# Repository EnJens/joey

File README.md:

# Joey 

Joey is an ECP5 with a 50-pin FPC connector intended to be used as a 
breakout development board for high-pin count usecases.

Ideas includes:
* RGB data (e.g. RGB <-> HDMI)
* Retro console Flashcarts

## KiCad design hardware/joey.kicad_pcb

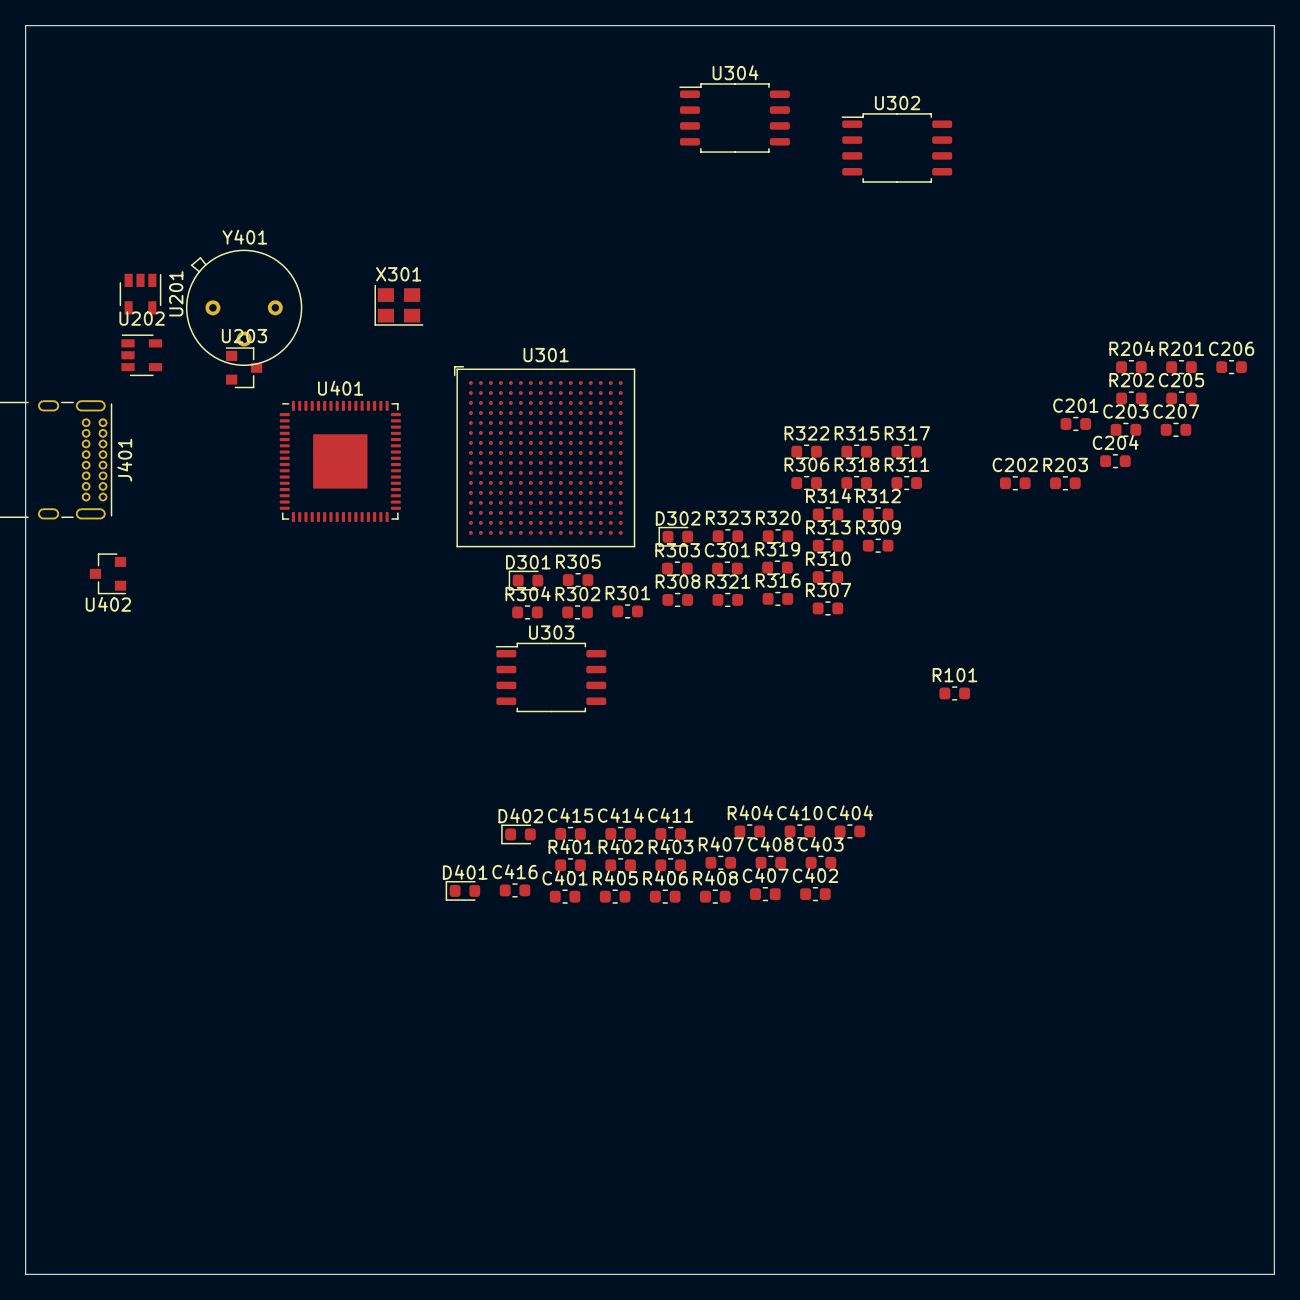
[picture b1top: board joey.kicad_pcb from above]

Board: 4 copper layers, 100.0 x 100.0 mm, 71 parts (0 on the bottom side), 50 nets, no tracks yet.

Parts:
C201, C202, C205, C206: 10uF; C_0603_1608Metric
C203, C204: 22pF; C_0603_1608Metric
C207: 1uF; C_0603_1608Metric
C301, C404, C407, C408, C410, C411, C414, C415: 0.1uF; C_0603_1608Metric
C401, C403: C_Small; C_0603_1608Metric
C402, C416: 4.7uF; C_0603_1608Metric
D301: Red; LED_0603_1608Metric
D302: Green; LED_0603_1608Metric
D401, D402: G; LED_0603_1608Metric
J401: USB_C_Receptacle_USB2.0; USB_C_Receptacle_GCT_USB4085
R101: 0R; R_0603_1608Metric
R201: 1.5k; R_0603_1608Metric
R202: 120k; R_0603_1608Metric
R203: 6.8k; R_0603_1608Metric
R204: 100k; R_0603_1608Metric
R301, R312, R313: 1k; R_0603_1608Metric
R302, R314, R315: 4.7k; R_0603_1608Metric
R303, R304: 360R; R_0603_1608Metric
R305, R306, R307, R308, R309, R310, R311, R316, R317, R318, R319, R320, R321, R322, R323, R404: 10k; R_0603_1608Metric
R401, R402: 5.1k; R_0603_1608Metric
R403: 12k 1%; R_0603_1608Metric
R405, R406: 360; R_0603_1608Metric
R407, R408: 27R; R_0603_1608Metric
U201, U202: M2406-ADJ; SOT-23-5
U203: XC6206P25; SOT-23
U301: LFE5U-12F-6BG256C; BGA-256_14.0x14.0mm_Layout16x16_P0.8mm_Ball0.45mm_Pad0.32mm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
U302, U304: LY68L6400SLIT; SOIC-8_5.23x5.23mm_P1.27mm
U303: W25Q32JVSS; SOIC-8_5.23x5.23mm_P1.27mm
U401: FT2232HQ; QFN-64-1EP_9x9mm_P0.5mm_EP4.35x4.35mm
U402: XC6206PxxxMR; SOT-23
X301: 25Mhz; Oscillator_SMD_Abracon_ASE-4Pin_3.2x2.5mm
Y401: 12Mhz; Crystal_HC35-U

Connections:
+1V1: C204.1, C206.1, R204.1, U301.G6, U301.G7, U301.G9, U301.L8, U301.L9, U301.L10
+1V8: C407.1, C408.1, C416.1, U401.12, U401.37, U401.49, U401.64
+2V5: C207.1, U203.2, U301.G11, U301.L7
+3V3: C410.1, C411.1, R404.2
/fpga/FLASH_CLK: R312.2, U301.N9, U303.6
/fpga/FLASH_IO0: R316.2, U301.T8, U303.5
/fpga/FLASH_IO1: R318.2, U301.T7, U303.2
/fpga/FLASH_IO2: R320.2, U301.M7, U303.3
/fpga/FLASH_IO3: R322.2, U301.N7, U303.7
/fpga/FPGA_DONE: R304.1, U301.P9
/fpga/FPGA_INITN: R303.1, R305.2, U301.T9
/fpga/RAM0_CLK: R301.2, U302.6
/fpga/RAM0_IO0: R306.2, U302.5
/fpga/RAM0_IO1: R307.2, U302.2
/fpga/RAM0_IO2: R308.2, U302.3
/fpga/RAM0_IO3: R309.2, U302.7
/fpga/RAM1_CLK: R313.2, U304.6
/fpga/RAM1_IO0: R317.2, U304.5
/fpga/RAM1_IO1: R319.2, U304.2
/fpga/RAM1_IO2: R321.2, U304.3
/fpga/RAM1_IO3: R323.2, U304.7
/fpga/~FLASH_CS~: R314.2, U301.R8, U303.1
/fpga/~RAM0_CS~: R302.2, U302.1
/fpga/~RAM1_CS~: R315.2, U304.1
/power/3.3v: C203.1, C205.1, C301.2, D301.2, D302.2, R203.1, R301.1, R302.1, R305.1, R306.1, R307.1, R308.1, R309.1, R310.1, R311.1, R312.1, R313.1, R314.1, R315.1, R316.1, R317.1, R318.1, R319.1, R320.1, R321.1, R322.1, R323.1, U203.3, U301.L6, U302.8, U303.8, U304.8, X301.1, X301.4
/usb/CC1: J401.A5, R401.2
/usb/CC2: J401.B5, R402.2
/usb/D+: J401.A6, J401.B6, R408.1
/usb/D-: J401.A7, J401.B7, R407.1
/usb/FTDI_D+: R408.2, U401.8
/usb/FTDI_D-: R407.2, U401.7
/usb/OSCI: C401.1, U401.2, Y401.1
/usb/OSCO: C403.1, U401.3, Y401.3
/usb/REF: R403.1, U401.6
/usb/RXLED: R406.2, U401.30
/usb/TXLED: R405.2, U401.29
/usb/VPHY: C402.1, C404.1, U401.4, U401.9
/usb/~RESET~: R404.1, U401.14
/usb/~SUSPEND~: R101.2, U401.36
GND: C201.2, C202.2, C205.2, C206.2, C207.2, C301.1, C401.2, C402.2, C403.2, C404.2, C407.2, C408.2, C410.2, C411.2, C414.2, C415.2, C416.2, J401.A1, J401.A12, J401.B1, J401.B12, J401.S1, R101.1, R201.1, R202.1, R401.1, R402.1, R403.2, U201.1, U201.2, U202.1, U202.2, U203.1, U301.A1, U301.A16, U301.D2, U301.D15, U301.F8, U301.F9, U301.G8, U301.G10, U301.H1, U301.H8, U301.H9, U301.H10, U301.H16, U301.J8, U301.J9, U301.J10, U301.K6, U301.K7, U301.K8, U301.K9, U301.K10, U301.N2, U301.N10, U301.N15, U301.R10, U301.T1, U301.T5, U301.T12, U301.T16, U302.4, U303.4, U304.4, U401.1, U401.5, U401.10, U401.11, U401.13, U401.15, U401.25, U401.35, U401.47, U401.51, U401.65, U402.1, X301.2
unnamed: C203.2, R201.2, R203.2, U201.5
unnamed: C204.2, R202.2, R204.2, U202.5
unnamed: D301.1, R303.2
unnamed: D302.1, R304.2
unnamed: D401.1, R405.1
unnamed: D402.1, R406.1
unnamed: R310.2, U301.P10
unnamed: R311.2, U301.R9
VBUS: C201.1, C202.1, C414.1, J401.A4, J401.A9, J401.B4, J401.B9, U201.4, U202.4, U402.3
VDD_FTDI: C415.1, D401.2, D402.2, U401.20, U401.31, U401.42, U401.50, U401.56, U402.2

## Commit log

2020-07-01 Start building power supply, usb
2020-07-02 Finish FTDI schematic, add datasheets
2020-07-03 Add oscilator datasheet
2020-07-03 Add oscilator, flash, ram
2020-07-08 More stuff
